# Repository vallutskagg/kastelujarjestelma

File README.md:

# Watering System

ESP32- ja ESP-IDF-pohjainen automaattinen kastelujärjestelmä. Järjestelmä
mittaa maan kosteutta ja ulkolämpötilaa, tarkkailee vesisäiliön tasoa ja ohjaa
vesipumppua releen kautta. Mittaus- ja ohjaustiedot välitetään MQTT:lla.

Tämä README sisältää kokoamis-, asennus-, kalibrointi-, käyttö- ja
GitHub-ohjeet, joiden avulla toinen käyttäjä voi ottaa projektin käyttöön.

## Sisältö

- [Toimintaperiaate](#toimintaperiaate)
- [Tarvittavat osat](#tarvittavat-osat)
- [Kytkennät](#kytkennät)
- [Ohjelmiston asennus](#ohjelmiston-asennus)
- [Asetukset](#asetukset)
- [Kalibrointi](#kalibrointi)
- [MQTT-käyttö](#mqtt-käyttö)
- [Testaus](#testaus)
- [PCB- ja kotelotiedostot](#pcb--ja-kotelotiedostot)
- [Vianhaku](#vianhaku)

## Toimintaperiaate

ESP32 suorittaa seuraavaa toimintalogiikkaa:

1. Laite käynnistää releen pois päältä, alustaa anturit ja yhdistää 2,4 GHz
   Wi-Fi-verkkoon sekä MQTT-brokeriin.
2. Maankosteusanturista luetaan useita ADC-näytteitä ja niiden keskiarvo.
3. Jos ADC-arvo ylittää kuivuusrajan riittävän monta peräkkäistä kertaa, maa
   tulkitaan kuivaksi.
4. Pumppu käynnistetään vain, jos pumpun ohjaus on sallittu, kastelujen välinen
   turva-aika on kulunut ja säiliöanturi ei ilmoita veden olevan vähissä.
5. Pumppu käy asetetun ajan ja sammuu automaattisesti.
6. DS18B20-lämpötila, maankosteus, säiliön tila ja pumpun tila julkaistaan
   MQTT:lla.
7. Pumppua, mittausta ja kasteluaikaa voi ohjata myös MQTT-komennoilla.

Säiliön tila `LOW` estää sekä automaattisen että manuaalisen pumppauksen.
Tila `UNKNOWN` ei nykyisessä ohjelmassa estä pumppausta. Jos säiliöanturi ei ole
kytketty tai toimii väärin, pumppua saa käyttää vain valvotusti.

Releohjaus on active-low:

- `GPIO26 = HIGH`: rele ja pumppu pois päältä
- `GPIO26 = LOW`: rele ja pumppu päällä

Kastelujen välinen turva-aika tallennetaan vain ESP32:n muistiin. Laitteen
uudelleenkäynnistys nollaa viimeisen kastelun ajan.

## Projektin rakenne

| Polku | Sisältö |
| --- | --- |
| [`main/`](main/) | ESP32-ohjelmiston lähdekoodi ja asetukset |
| [`hardware/pcb/`](hardware/pcb/) | KiCad-projekti ja piirilevyn lähdetiedostot |
| [`hardware/enclosure/`](hardware/enclosure/) | OpenSCAD-kotelomalli |
| [`PCB_OHJE.md`](PCB_OHJE.md) | PCB:n yksityiskohtaiset suunnitteluohjeet |
| [`GITHUB_OHJE.md`](GITHUB_OHJE.md) | Git- ja GitHub-työskentelyohje |
| `pump_test_values_backup_2026-04-10.txt` | Aiemmat pumpun testiasetukset |

## Tarvittavat osat

Pakolliset osat:

- ESP32 DevKit, jota ESP-IDF tukee
- kapasitiivinen maankosteusanturi, analoginen `0-3,0 V` ulostulo
- active-low-yhteensopiva 1-kanavainen 5 V relemoduuli
- 3-5 V DC-vesipumppu ja sopiva letku
- kapasitiivinen säiliön tasoanturi digitaalisella ulostulolla
- virtalähde pumpulle ja releelle
- johdot ja liittimet

Suositellut tai valinnaiset osat:

- DS18B20-lämpötila-anturi
- `4,7 kOhm` vastus DS18B20 DATA-linjan ja `3V3`:n väliin
- LED ja `330 Ohm` sarjavastus säiliön alhaisen tason ilmaisimeksi
- `100 nF` ohituskondensaattorit antureiden syöttöihin
- projektin KiCad-piirilevy ja 3D-tulostettu kotelo

Katso tarkempi komponentti- ja liitinluettelo tiedostosta
[`PCB_OHJE.md`](PCB_OHJE.md).

## Kytkennät

### ESP32-signaalit

| Toiminto | ESP32-pinni | Huomio |
| --- | --- | --- |
| Releen ohjaus | `GPIO26` | Active-low |
| Maankosteusanturin AO | `GPIO34` | ADC1 channel 6, enintään 3,3 V |
| DS18B20 DATA | `GPIO4` | `4,7 kOhm` pull-up vastus `3V3`:een |
| Säiliön tasoanturin signaali | `GPIO27` | Oletuksena HIGH tarkoittaa vettä |
| Säiliön tason LED | `GPIO25` | Oletuksena LED syttyy, kun säiliö on LOW |

### Peruskytkentä

- Kytke ESP32:n, relemoduulin, antureiden ja pumpun virtalähteen maat yhteen.
- Kytke maankosteusanturi `3V3`:een. Älä syötä yli 3,3 V signaalia
  `GPIO34`:aan.
- Kytke DS18B20 `3V3`:een ja lisää DATA-linjalle `4,7 kOhm` pull-up-vastus.
- Kytke relemoduulin `IN` pinniin `GPIO26`.
- Kytke pumpun virtapiiri releen `COM`- ja `NO`-kontaktien kautta.
- Kytke säiliöanturi valmistajan pinijärjestyksen mukaisesti. Tarkista
  johdinvärit ennen virran kytkemistä.

Tarkat netit, liittimet, jännitteet ja PCB-layout-ohjeet ovat tiedostossa
[`PCB_OHJE.md`](PCB_OHJE.md).

## Ohjelmiston asennus

### 1. Asenna työkalut

Tarvitset:

- Git
- Espressif ESP-IDF
- USB-ajurin omalle ESP32-kehityskortille
- datansiirtoa tukevan USB-kaapelin

Windowsissa helpoin tapa on asentaa Espressif IDF Installer ja avata sen
luoma **ESP-IDF PowerShell**, jossa `idf.py` on käytettävissä.

### 2. Lataa projekti

```powershell
git clone https://github.com/vallutskagg/kastelujarjestelma.git
cd kastelujarjestelma
```

### 3. Valitse kohde ja aseta tunnukset

```powershell
idf.py set-target esp32
idf.py menuconfig
```

Avaa valikko **Watering System** ja aseta ainakin:

- `WiFi SSID`
- `WiFi password`
- `MQTT broker URI`
- yksilöllinen `MQTT client id`
- MQTT-käyttäjätunnus ja salasana, jos broker vaatii ne

Wi-Fi- ja MQTT-salaisuudet tallentuvat paikalliseen `sdkconfig`-tiedostoon.
Tiedosto on ohitettu Gitissa, eikä sitä pidä julkaista GitHubiin.

Jos käytät julkista MQTT-brokeria, muuta kaikki MQTT-topic-nimet
yksilöllisiksi. Muuten muut saman brokerin käyttäjät voivat nähdä viestejä tai
lähettää pumppukomentoja.

### 4. Käännä ja siirrä ohjelma

```powershell
idf.py build
idf.py -p COM3 flash monitor
```

Korvaa `COM3` oman ESP32-laitteesi portilla. Sulje sarjamonitori
ESP-IDF:n pikanäppäimellä `Ctrl+]`.

Onnistuneessa käynnistyksessä lokissa näkyy muun muassa Wi-Fi- ja
MQTT-yhteys, antureiden alustus sekä kosteusmittauksia.

## Asetukset

Asetuksia muokataan komennolla `idf.py menuconfig` valikosta
**Watering System**.

| Asetus | Oletus | Merkitys |
| --- | ---: | --- |
| `WATERING_DRY_THRESHOLD` | `3000` | Tämän ylittävä ADC-arvo tulkitaan kuivaksi |
| `WATERING_MOISTURE_WET_ADC` | `1500` | 0 prosentin kuivuuden kalibrointipiste |
| `WATERING_MOISTURE_DRY_ADC` | `3200` | 100 prosentin kuivuuden kalibrointipiste |
| `WATERING_PUMP_ON_MS` | `8000` | Pumpun oletuskäyntiaika millisekunteina |
| `WATERING_CHECK_INTERVAL_MS` | `60000` | Maankosteuden automaattinen mittausväli |
| `WATERING_DRY_CONSECUTIVE_READS` | `3` | Vaaditut peräkkäiset kuivat mittaukset |
| `WATERING_MIN_WATERING_INTERVAL_HOURS` | `72` | Kastelujen välinen turva-aika |
| `WATERING_ADC_SAMPLES` | `8` | Keskiarvoon käytettävien ADC-näytteiden määrä |
| `WATERING_TEMP_READ_INTERVAL_MS` | `10000` | Lämpötilan mittausväli |
| `WATERING_MQTT_CMD_ARM_DELAY_MS` | `5000` | MQTT-komentojen esto yhdistämisen jälkeen |

Ensimmäinen testaus kannattaa tehdä lyhyellä pumpun käyntiajalla ja ilman,
että letku osoittaa kasviin. Aseta lopulliset arvot kasvin, ruukun, pumpun ja
anturin mittausten perusteella.

## Kalibrointi

Maankosteusanturin ADC-arvot riippuvat anturista, maaperästä ja sijoituksesta.
Kalibroi jokainen asennus erikseen:

1. Avaa sarjamonitori komennolla `idf.py monitor`.
2. Mittaa anturi kuivassa tai kuivassa mullassa ja kirjaa lokin
   `Soil ADC avg` -arvo.
3. Mittaa anturi hyvin kosteassa mullassa ja kirjaa arvo.
4. Aseta kuiva arvo kohtaan `WATERING_MOISTURE_DRY_ADC`.
5. Aseta märkä arvo kohtaan `WATERING_MOISTURE_WET_ADC`.
6. Valitse `WATERING_DRY_THRESHOLD` kuivan ja märän arvon väliltä.
7. Testaa usean päivän ajan valvotusti ennen automaattisen kastelun käyttöä.

Tässä projektissa suurempi ADC-arvo tarkoittaa oletuksena kuivempaa maata.
Anturia ei saa upottaa elektroniikkaosan yli.

## MQTT-käyttö

Oletusbroker on vain kehitystä varten `mqtt://broker.hivemq.com`. Omaan
jatkuvaan käyttöön suositellaan salasanalla ja TLS-yhteydellä suojattua
brokeria, esimerkiksi paikallista Mosquitto-palvelinta.

### Julkaistavat topicit

| Topic | Sisältö |
| --- | --- |
| `watering_system/soil` | JSON: kosteus, kuivuusprosentti, lämpötila ja ajat |
| `watering_system/soil/raw` | Maankosteuden ADC-raaka-arvo |
| `watering_system/soil/dry_percent` | Kuivuus `0-100` prosenttia |
| `watering_system/temperature/outdoor_c` | DS18B20-lämpötila Celsius-asteina |
| `watering_system/status/pump_duration_s` | Pumpun aktiivinen käyntiaika |
| `watering_system/status/pump_enable` | `ON` tai `OFF` |
| `watering_system/status/pump_running` | `ON` tai `OFF` |
| `watering_system/status/tank_level` | `FULL`, `LOW` tai `UNKNOWN` |
| `watering_system/status/tank_level_raw` | `1`, `0` tai `-1` |

Esimerkki `watering_system/soil`-viestistä:

```json
{
  "moisture": 2875,
  "dry_percent": 81,
  "temperature_c": 21.50,
  "dry_threshold": 3000,
  "ts": 1781000000,
  "last_watering_ts": 0,
  "last_watering_local": "never"
}
```

### Vastaanotettavat komennot

| Topic | Hyväksytty viesti | Toiminto |
| --- | --- | --- |
| `watering_system/cmd/pump_duration_s` | kokonaisluku, oletuksena `8-20` | Muuttaa pumpun käyntiaikaa |
| `watering_system/cmd/pump_manual` | `RUN`, `ON`, `1` tai `START` | Käynnistää manuaalisen kastelun |
| `watering_system/cmd/pump_enable` | `ON`, `OFF`, `1` tai `0` | Sallii tai estää pumpun |
| `watering_system/cmd/measure_now` | `READ`, `MEASURE`, `ON` tai `1` | Julkaisee uuden kosteusmittauksen |

Esimerkit Mosquitto-työkaluilla:

```powershell
mosquitto_sub -h BROKERIN_OSOITE -t "watering_system/#" -v
mosquitto_pub -h BROKERIN_OSOITE -t "watering_system/cmd/measure_now" -m "READ"
mosquitto_pub -h BROKERIN_OSOITE -t "watering_system/cmd/pump_enable" -m "OFF"
```

Pumpun manuaalinen käynnistys:

```powershell
mosquitto_pub -h BROKERIN_OSOITE -t "watering_system/cmd/pump_manual" -m "RUN"
```

Suorita manuaalinen pumppukomento vain, kun laite ja veden kulku ovat
valvottuja.

## Testaus

Tee testit tässä järjestyksessä:

1. Tarkista kaikki jännitteet ja polariteetit yleismittarilla ilman ESP32:ta.
2. Käynnistä ESP32 ilman pumppua ja tarkista sarjaloki.
3. Tarkista maankosteuden raaka-arvo kuivassa ja kosteassa mullassa.
4. Tarkista DS18B20:n lämpötila.
5. Tarkista, että säiliöanturin tilat `FULL` ja `LOW` vaihtuvat oikein.
6. Tarkista ilman pumppua, että rele kytkeytyy active-low-logiikalla.
7. Testaa pumppu lyhyesti erillään kasvista.
8. Tarkista, että `LOW`-säiliötila estää pumppauksen.
9. Testaa lopuksi automaattikastelu valvotusti.

Releelle on `menuconfig`-valikossa jatkuva self-test-tila. Kun se on käytössä,
normaali kastelulogiikka ei käynnisty. Älä jätä self-test-tilaa päälle
varsinaiseen käyttöön.

## PCB- ja kotelotiedostot

### Esikatselut

#### Schematic

*Kuva 1. Kastelujärjestelmän KiCad-kytkentakaavio. Kaavio sisältää ESP32:n,
maankosteusanturin, DS18B20-lämpötila-anturin, säiliön tasoanturin, LEDin ja
releen ohjausliitännän.*

#### PCB-layout

*Kuva 2. Kastelujärjestelmän kaksipuolinen PCB-layout. Punainen kuvaa
etupuolen kuparia ja sininen takapuolen kuparia.*

#### PCB:n 3D-näkymä

*Kuva 3. KiCadin 3D-layout piirilevystä. Kuvassa näkyvät piirilevyn
komponenttien ja liittimien sijoittelu sekä kuparivetojen reititys.*

#### Kotelon 3D-malli

*Kuva 4. OpenSCADilla mallinnettu kotelon pohja ja irrotettava kansi.*

Kuvat näkyvät automaattisesti GitHubissa, kun ne tallennetaan näihin
tiedostopolkuihin ja lisätään Git-versionhallintaan. KiCad-kuvien vientiohjeet
ovat kansiossa [`hardware/pcb/previews/`](hardware/pcb/previews/).

### Mihin tiedostot lisätään

Tallenna muokattavat KiCad-lähdetiedostot tähän kansioon:

```text
hardware/pcb/
```

Nykyiset KiCad-tiedostot:

```text
hardware/pcb/kastelujarjestelma_pcb_ja_schematic/
  irrigation_esp32_J8J9_KUVAN_MUKAINEN.kicad_pro
  irrigation_esp32_J8J9_KUVAN_MUKAINEN.kicad_sch
  irrigation_esp32_J8J9_KUVAN_MUKAINEN.kicad_pcb
  pcb.kicad_pro
  pcb.kicad_pcb
```

Avaa KiCad-projekti ensisijaisesti `.kicad_pro`-tiedostosta. Projektikohtaiset
KiCad-symbolit, footprintit ja kirjastotaulukot kuuluvat samaan kansioon.

Tallenna muokattava OpenSCAD-kotelomalli tähän kansioon:

```text
hardware/enclosure/esp32_kastelu_kotelo.scad
```

Kun tiedostot on lisätty ja julkaistu GitHubiin, käyttäjä voi:

- selata ja ladata lähdetiedostoja kansioista
  [`hardware/pcb/`](hardware/pcb/) ja
  [`hardware/enclosure/`](hardware/enclosure/)
- ladata koko projektin GitHubin **Code > Download ZIP** -toiminnolla
- kloonata projektin komennolla `git clone`
- avata KiCad-lähteet KiCadissa ja `.scad`-tiedoston OpenSCADissa

GitHub näyttää `.scad`-tiedoston tekstinä. KiCad-tiedostoja voi tarkastella
tekstinä, mutta varsinainen schema ja piirilevy avataan KiCadissa.

Jos haluat suunnitelmien olevan helposti tarkasteltavissa suoraan GitHubissa,
vie niistä esikatselukuvat ja tallenna ne versionhallintaan:

```text
hardware/pcb/previews/schematic.png
hardware/pcb/previews/pcb-layout.png
hardware/pcb/previews/3d_pcb_layout.png
hardware/enclosure/previews/kotelo.png
```

PNG- ja SVG-kuvat näkyvät suoraan GitHubin sivulla. Lisää esikatselukuvat
normaalisti Gitiin yhdessä lähdetiedostojen kanssa.

### Valmistus- ja tulostustiedostot

KiCadista generoidut Gerber-, poraus-, BOM- ja pick-and-place-tiedostot
kuuluvat paikallisesti kansioon:

```text
hardware/pcb/generated/
```

OpenSCADista generoidut STL- ja 3MF-tiedostot kuuluvat paikallisesti kansioon:

```text
hardware/enclosure/generated/
```

Nämä `generated/`-kansiot on ohitettu Gitissa. Kun suunnitelma on valmis,
pakkaa valmistustiedostot ZIP-tiedostoiksi ja liitä ne GitHub Releasen
ladattaviksi. Tällä tavalla:

- GitHub-repositorio sisältää aina muokattavat KiCad- ja OpenSCAD-lähteet
- Release sisältää tiettyyn versioon kuuluvat valmiit Gerber- ja STL-tiedostot
- toinen käyttäjä voi joko muokata suunnitelmaa tai ladata valmiin version

Tiedostojen lisääminen Gitiin:

```powershell
git add hardware/pcb hardware/enclosure README.md
git status
git commit -m "Add PCB design and enclosure model"
git push
```

Tarkempi julkaisuohje on tiedostossa [`GITHUB_OHJE.md`](GITHUB_OHJE.md).

## Vianhaku

**`idf.py`-komentoa ei löydy**

Avaa Espressif-asennuksen luoma ESP-IDF PowerShell tai aktivoi ESP-IDF-
ympäristö ennen komentojen suorittamista.

**ESP32 ei yhdistä Wi-Fiin**

Varmista, että verkko on 2,4 GHz ja SSID sekä salasana on asetettu
`idf.py menuconfig` -valikossa.

**MQTT-yhteys ei toimi**

Tarkista brokerin URI, portti, tunnukset, palomuuri ja TLS-asetukset.

**Maankosteusarvo ei muutu**

Tarkista anturin `AO`, `VCC` ja `GND`, mittaa `AO` yleismittarilla ja varmista,
että signaali on kytketty `GPIO34`:aan.

**Pumppu ei käynnisty**

Tarkista MQTT:n `pump_enable`, säiliön tila, releen active-low-logiikka,
pumpun erillinen syöttö ja yhteinen maa.

**Pumppu käynnistyy väärin päin**

Nykyinen ohjelma olettaa active-low-releen. Älä jatka käyttöä ennen kuin releen
logiikka ja turvallinen alkutila on korjattu.

**DS18B20 ei anna lämpötilaa**

Tarkista johdinjärjestys ja `4,7 kOhm` pull-up-vastus DATA-linjan ja `3V3`:n
välillä.

## Turvallisuus

- Testaa laite ja pumppu aina valvotusti ennen automaattista käyttöä.
- Varmista yhteinen maa, oikeat käyttöjännitteet ja riittävä virtalähde.
- Suojaa elektroniikka vedeltä ja suunnittele vuodon seuraukset etukäteen.
- Älä syötä yli 3,3 V jännitettä ESP32:n GPIO-pinneihin.
- Älä kytke 230 V verkkovirtaa tämän projektin releeseen ilman asianmukaista
  sähkösuunnittelua, eristyksiä ja kotelointia.
- Julkisessa MQTT-brokerissa kuka tahansa voi mahdollisesti nähdä tai lähettää
  viestejä. Käytä tuotantokäytössä suojattua brokeria ja yksilöllisiä topic-
  nimiä.

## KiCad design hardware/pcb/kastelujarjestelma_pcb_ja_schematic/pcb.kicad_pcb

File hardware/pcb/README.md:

# PCB design status

Nykyiset KiCad-lahdetiedostot:

- `kastelujarjestelma_pcb_ja_schematic/irrigation_esp32_J8J9_KUVAN_MUKAINEN.kicad_pro`
- `kastelujarjestelma_pcb_ja_schematic/irrigation_esp32_J8J9_KUVAN_MUKAINEN.kicad_sch`
- `kastelujarjestelma_pcb_ja_schematic/irrigation_esp32_J8J9_KUVAN_MUKAINEN.kicad_pcb`
- `kastelujarjestelma_pcb_ja_schematic/pcb.kicad_pro`
- `kastelujarjestelma_pcb_ja_schematic/pcb.kicad_pcb`

## Tarkistettu

- KiCad-tiedostomuoto on version 10.0 muodossa.
- PCB:n reunamitta on `105 x 70 mm`.
- Firmware-signaalit ovat PCB:ssa:
  - `GPIO4`: DS18B20
  - `GPIO25`: tankin LED
  - `GPIO26`: rele
  - `GPIO27`: tankin tasoanturi
  - `GPIO34`: maankosteusanturi
- PCB:ssa on kuparivedot ja GND-kuparialueet molemmilla kuparikerroksilla.
- Anturiliittimet `J4-J7` ja ESP32-liittimet `J8/J9` ovat mukana.

## Korjattava ennen PCB:n tilaamista

- Scheman ja PCB:n tiedostonimet eivat vastaa toisiaan.
- Pumpun virtaliittimet `J1`, `J2` ja relekontaktin liitin `J10` puuttuvat
  nykyisesta schemasta ja PCB:sta.
- `J3`-releliittimen pinni 3 on PCB:ssa `+3.3V`. Projektin
  `PCB_OHJE.md` suosittelee WayinTopin 5 V relemoduulille `USB_5V`:a.
  Tarkista kaytetyn relemoduulin vaatima jannite ja korjaa schema seka PCB.
- KiCad ERC ja DRC on ajettava KiCadissa ennen valmistustiedostojen vientia.
- ESP32 DevKitin fyysinen pinijarjestys, rivivali ja USB-liittimen sijainti on
  verrattava juuri kaytettavaan korttiin.

Nykyista PCB:ta ei tule tilata ennen naiden kohtien tarkistamista.

## GitHubiin tuotavat KiCad-tiedostot

Tuo projektiin:

- nykyista schemaa vastaava `.kicad_pro`
- `.kicad_sch`
- `.kicad_pcb`
- BOM-tiedosto, jos haluat osaluettelon ladattavaksi
- `component_placement_top.png` ja `pseudo_3d_render.png`, jos haluat
  lisakuvia GitHubiin
- Gerber ZIP GitHub Releasen liitteeksi, kun PCB on tarkistettu

Ala tuo tavalliseen Git-versionhallintaan:

- `.history/` ja `*-backups/`
- `*.kicad_prl` ja `*.kicad_pro.lck`
- `~*.kicad_pro.lck`
- irrallisia Gerber-kansioita, jos julkaiset Gerber ZIP:n Releasessa
- vanhoja tai eri versioon kuuluvia `.kicad_pro`, `.kicad_sch` ja
  `.kicad_pcb`-tiedostoja

`DRC.rpt`, `report.txt`, pinmap- ja kytkentaohjeet ovat valinnaisia. Tuo ne
vain, jos ne ovat ajan tasalla ja auttavat projektin kayttajaa.

## GitHub-esikatselut

Tallenna schematic-, layout- ja 3D-kuvat kansioon [`previews/`](previews/).
Kansion README sisaltaa kuvien vientiohjeet.

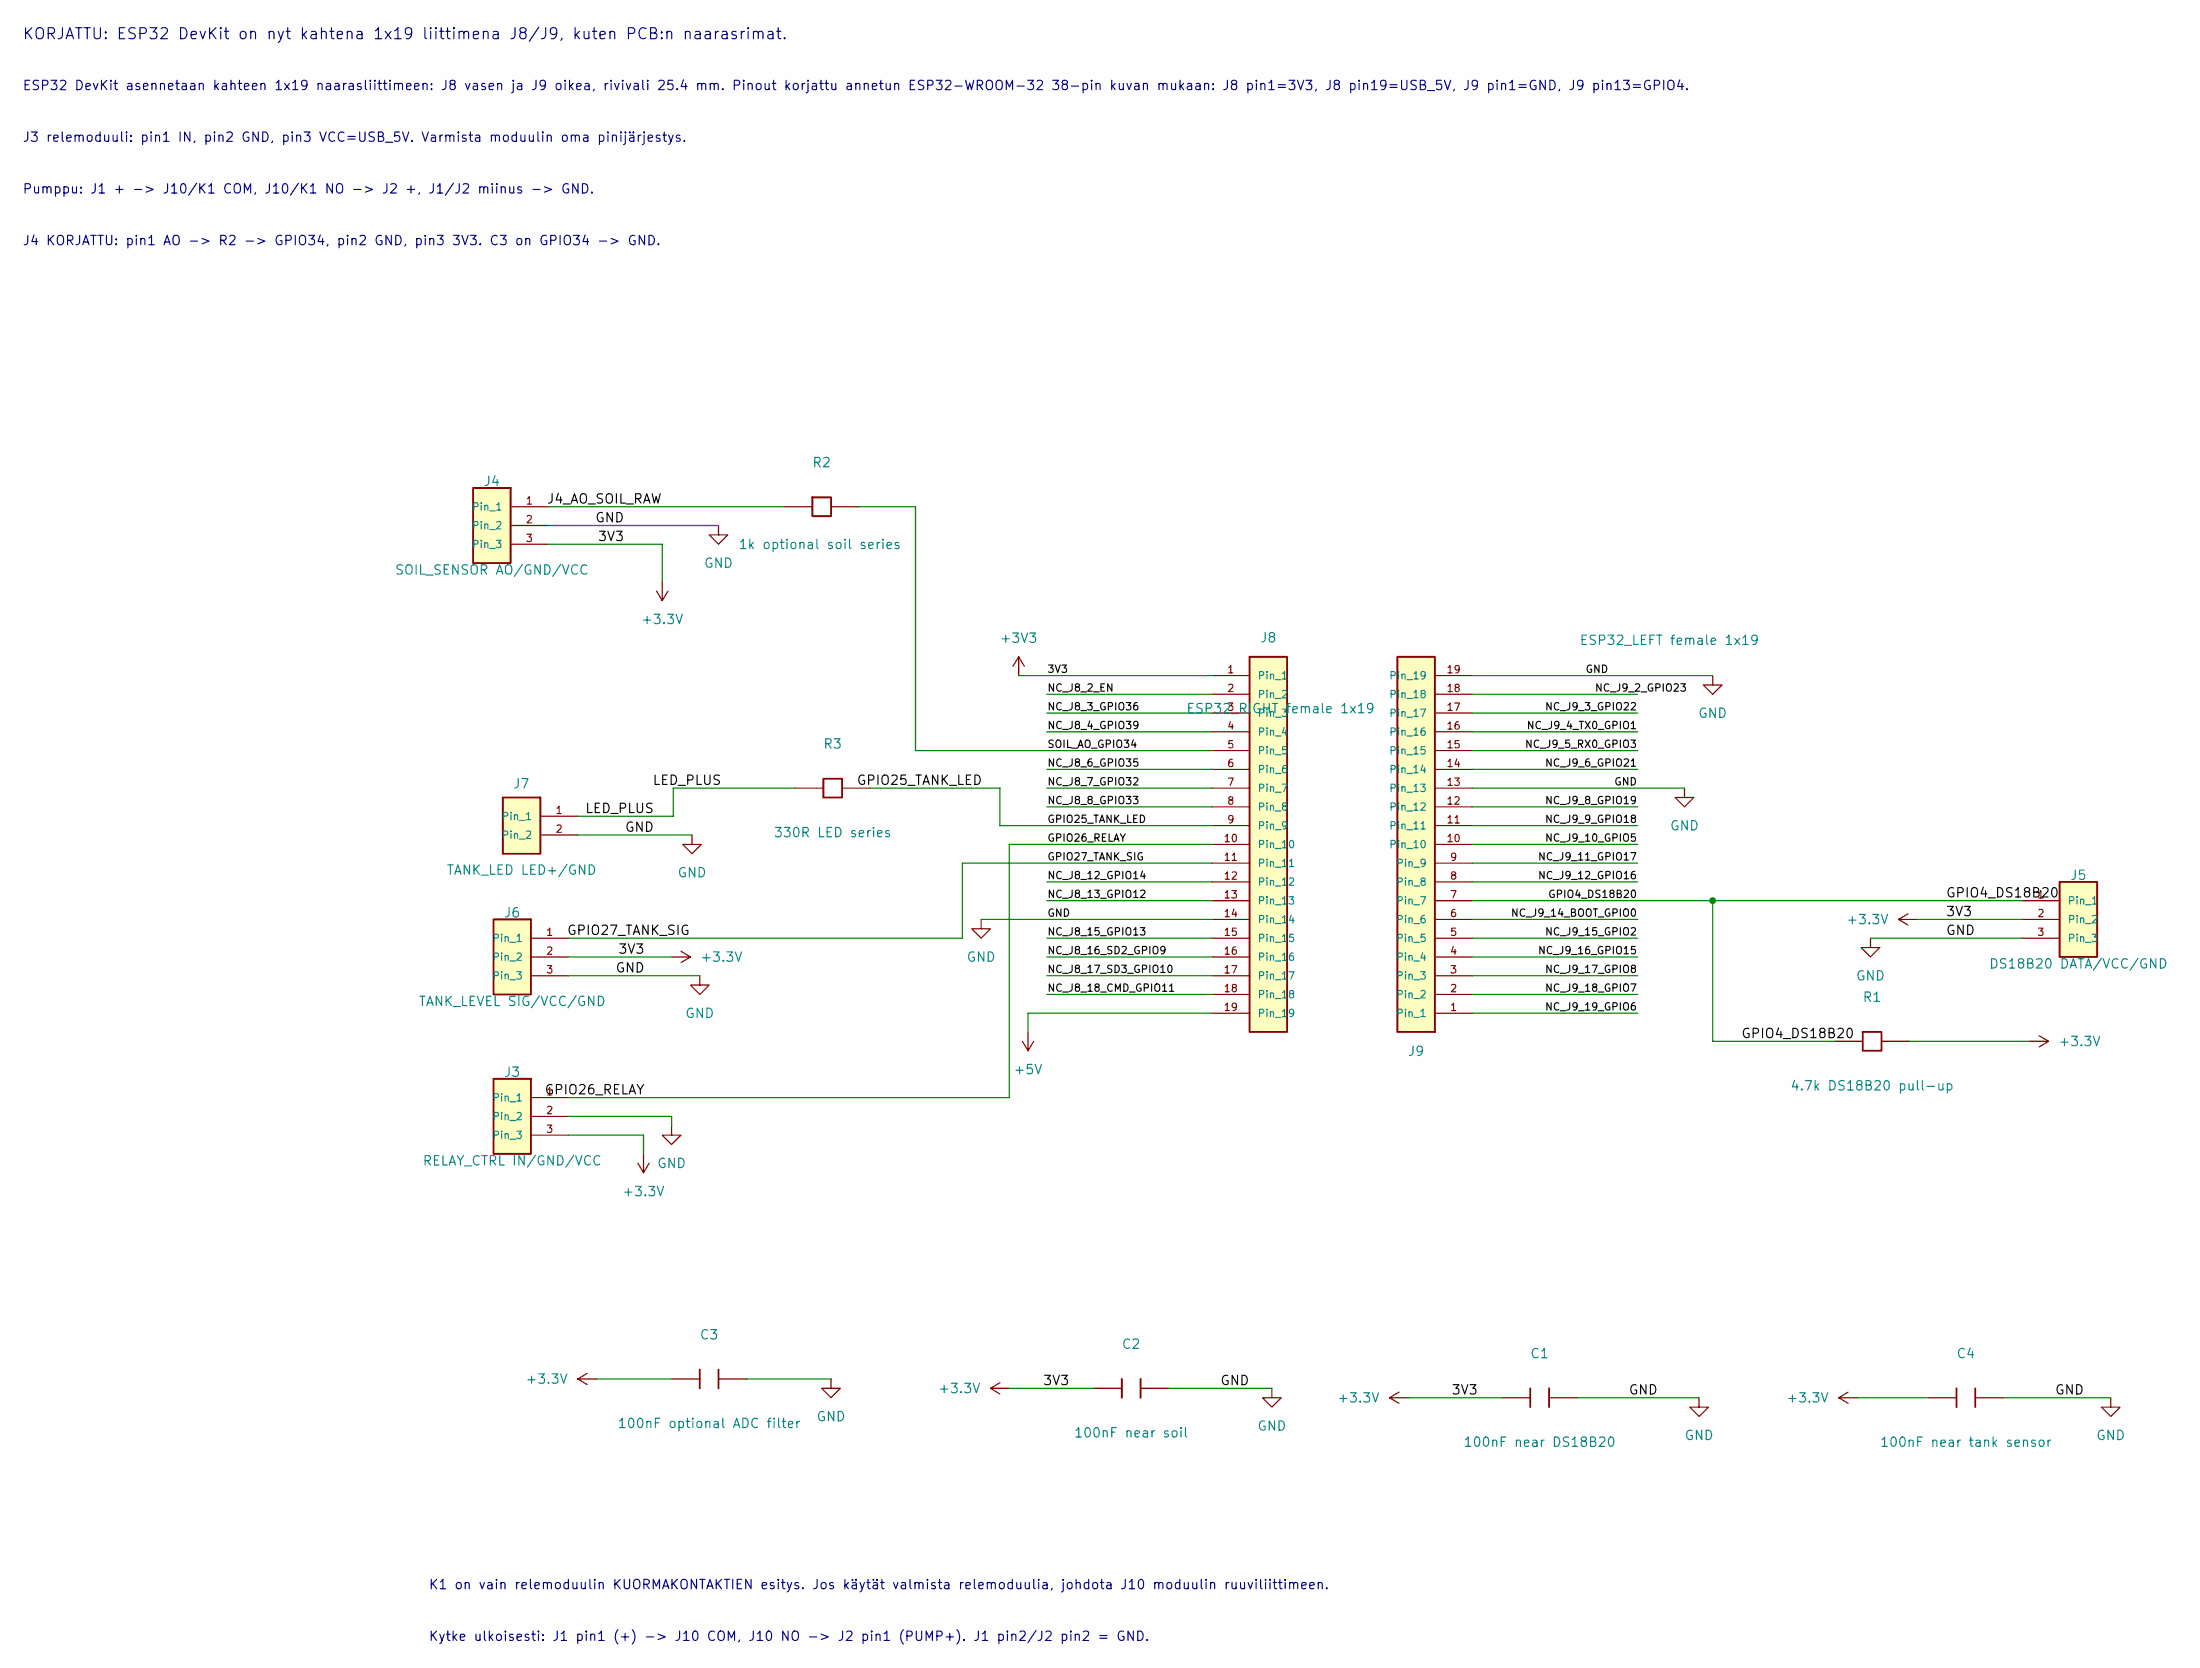
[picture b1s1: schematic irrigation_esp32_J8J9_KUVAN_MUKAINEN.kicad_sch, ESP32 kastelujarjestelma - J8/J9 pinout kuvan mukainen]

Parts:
C1: 100nF near DS18B20; C_Disc_D5.0mm_W2.5mm_P2.50mm
C2: 100nF near soil; C_Disc_D5.0mm_W2.5mm_P2.50mm
C3: 100nF optional ADC filter; C_Disc_D5.0mm_W2.5mm_P2.50mm
C4: 100nF near tank sensor; C_Disc_D5.0mm_W2.5mm_P2.50mm
J3: RELAY_CTRL IN/GND/VCC; PinHeader_1x03_P2.54mm_Vertical
J4: SOIL_SENSOR AO/GND/VCC; PinHeader_1x03_P2.54mm_Vertical
J5: DS18B20 DATA/VCC/GND; PinHeader_1x03_P2.54mm_Vertical
J6: TANK_LEVEL SIG/VCC/GND; PinHeader_1x03_P2.54mm_Vertical
J7: TANK_LED LED+/GND; PinHeader_1x02_P2.54mm_Vertical
J8: ESP32_LEFT female 1x19; PinSocket_1x19_P2.54mm_Vertical
J9: ESP32_RIGHT female 1x19; PinSocket_1x19_P2.54mm_Vertical
R1: 4.7k DS18B20 pull-up; R_Axial_DIN0207_L6.3mm_D2.5mm_P7.62mm_Horizontal
R2: 1k optional soil series; R_Axial_DIN0207_L6.3mm_D2.5mm_P7.62mm_Horizontal
R3: 330R LED series; R_Axial_DIN0207_L6.3mm_D2.5mm_P7.62mm_Horizontal

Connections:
+3.3V: C1.1, C2.1, C3.1, C4.1, J3.3, J4.3, J5.2, J6.2, J8.1, R1.2
+5V: J8.19
/GPIO4_DS18B20: J5.1, J9.7, R1.1
/GPIO25_TANK_LED: J8.9, R3.1
/GPIO26_RELAY: J3.1, J8.10
/GPIO27_TANK_SIG: J6.1, J8.11
/J4_AO_SOIL_RAW: J4.1, R2.1
/LED_PLUS: J7.1, R3.2
/NC_J8_2_EN: J8.2
/NC_J8_3_GPIO36: J8.3
/NC_J8_4_GPIO39: J8.4
/NC_J8_6_GPIO35: J8.6
/NC_J8_7_GPIO32: J8.7
/NC_J8_8_GPIO33: J8.8
/NC_J8_12_GPIO14: J8.12
/NC_J8_13_GPIO12: J8.13
/NC_J8_15_GPIO13: J8.15
/NC_J8_16_SD2_GPIO9: J8.16
/NC_J8_17_SD3_GPIO10: J8.17
/NC_J8_18_CMD_GPIO11: J8.18
/NC_J9_2_GPIO23: J9.18
/NC_J9_3_GPIO22: J9.17
/NC_J9_4_TX0_GPIO1: J9.16
/NC_J9_5_RX0_GPIO3: J9.15
/NC_J9_6_GPIO21: J9.14
/NC_J9_8_GPIO19: J9.12
/NC_J9_9_GPIO18: J9.11
/NC_J9_10_GPIO5: J9.10
/NC_J9_11_GPIO17: J9.9
/NC_J9_12_GPIO16: J9.8
/NC_J9_14_BOOT_GPIO0: J9.6
/NC_J9_15_GPIO2: J9.5
/NC_J9_16_GPIO15: J9.4
/NC_J9_17_GPIO8: J9.3
/NC_J9_18_GPIO7: J9.2
/NC_J9_19_GPIO6: J9.1
/SOIL_AO_GPIO34: J8.5, R2.2
GND: C1.2, C2.2, C3.2, C4.2, J3.2, J4.2, J5.3, J6.3, J7.2, J8.14, J9.13, J9.19

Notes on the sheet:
ESP32 DevKit asennetaan kahteen 1x19 naarasliittimeen: J8 vasen ja J9 oikea, rivivali 25.4 mm. Pinout korjattu annetun ESP32-WROOM-32 38-pin kuvan mukaan: J8 pin1=3V3, J8 pin19=USB_5V, J9 pin1=GND, J9 pin13=GPIO4.
J4 KORJATTU: pin1 AO -> R2 -> GPIO34, pin2 GND, pin3 3V3. C3 on GPIO34 -> GND.
Kytke ulkoisesti: J1 pin1 (+) -> J10 COM, J10 NO -> J2 pin1 (PUMP+). J1 pin2/J2 pin2 = GND.
K1 on vain relemoduulin KUORMAKONTAKTIEN esitys. Jos käytät valmista relemoduulia, johdota J10 moduulin ruuviliittimeen.
J3 relemoduuli: pin1 IN, pin2 GND, pin3 VCC=USB_5V. Varmista moduulin oma pinijärjestys.
Pumppu: J1 + -> J10/K1 COM, J10/K1 NO -> J2 +, J1/J2 miinus -> GND.
KORJATTU: ESP32 DevKit on nyt kahtena 1x19 liittimena J8/J9, kuten PCB:n naarasrimat.

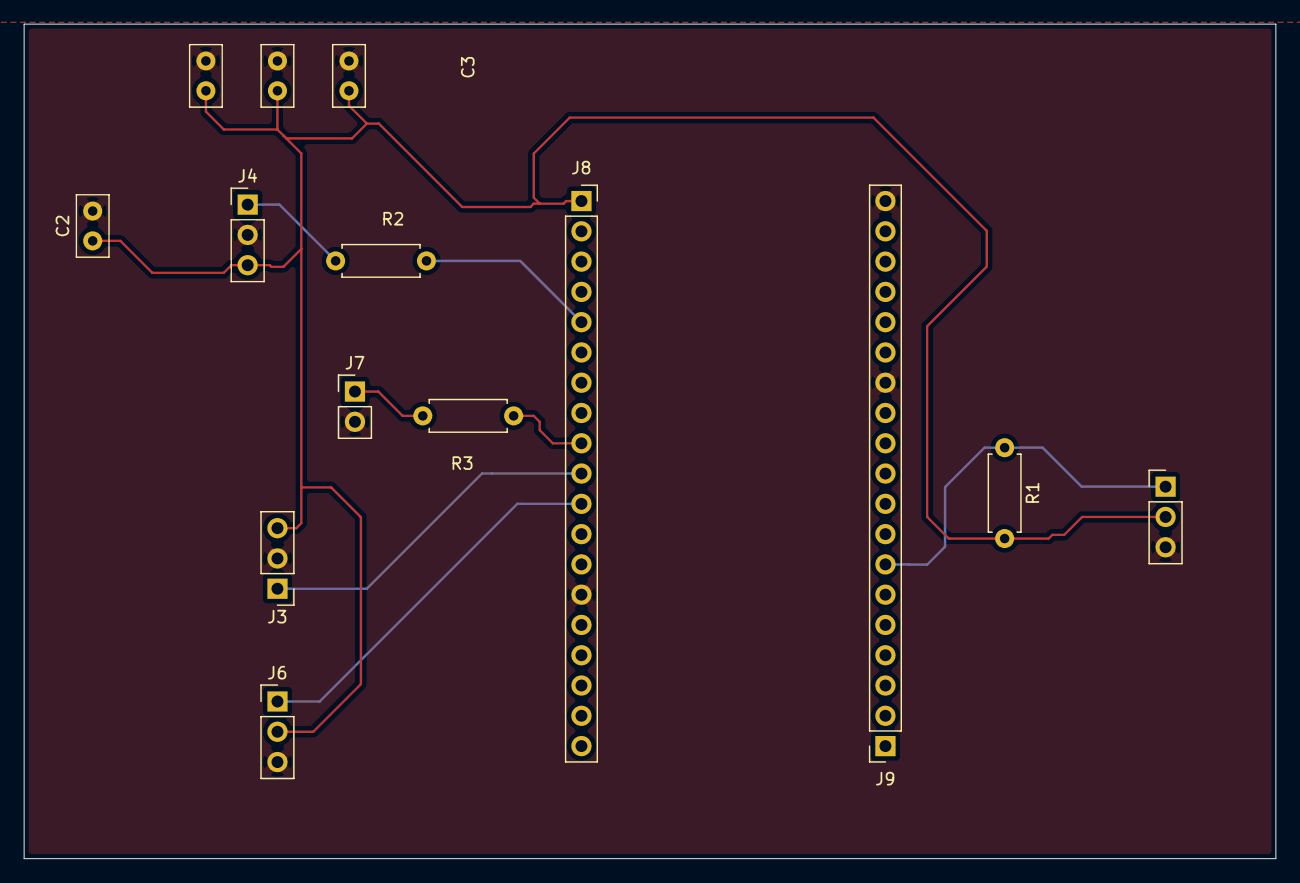
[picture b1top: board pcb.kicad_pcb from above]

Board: 2 copper layers, 105.0 x 70.0 mm, 14 parts (0 on the bottom side), 9 nets.

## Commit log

2026-06-09 Initial watering system project
2026-06-09 Fix GitHub and KiCad documentation
2026-06-09 Fix README Finnish characters
